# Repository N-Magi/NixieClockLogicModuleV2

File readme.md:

# NixieClockLogicModule v.2

new Version of NixieClock LogicModule mar fix wire ploblem

## How To Use

it's made from platformIo
open project as PIO project then connect to your microContoroller board and upload

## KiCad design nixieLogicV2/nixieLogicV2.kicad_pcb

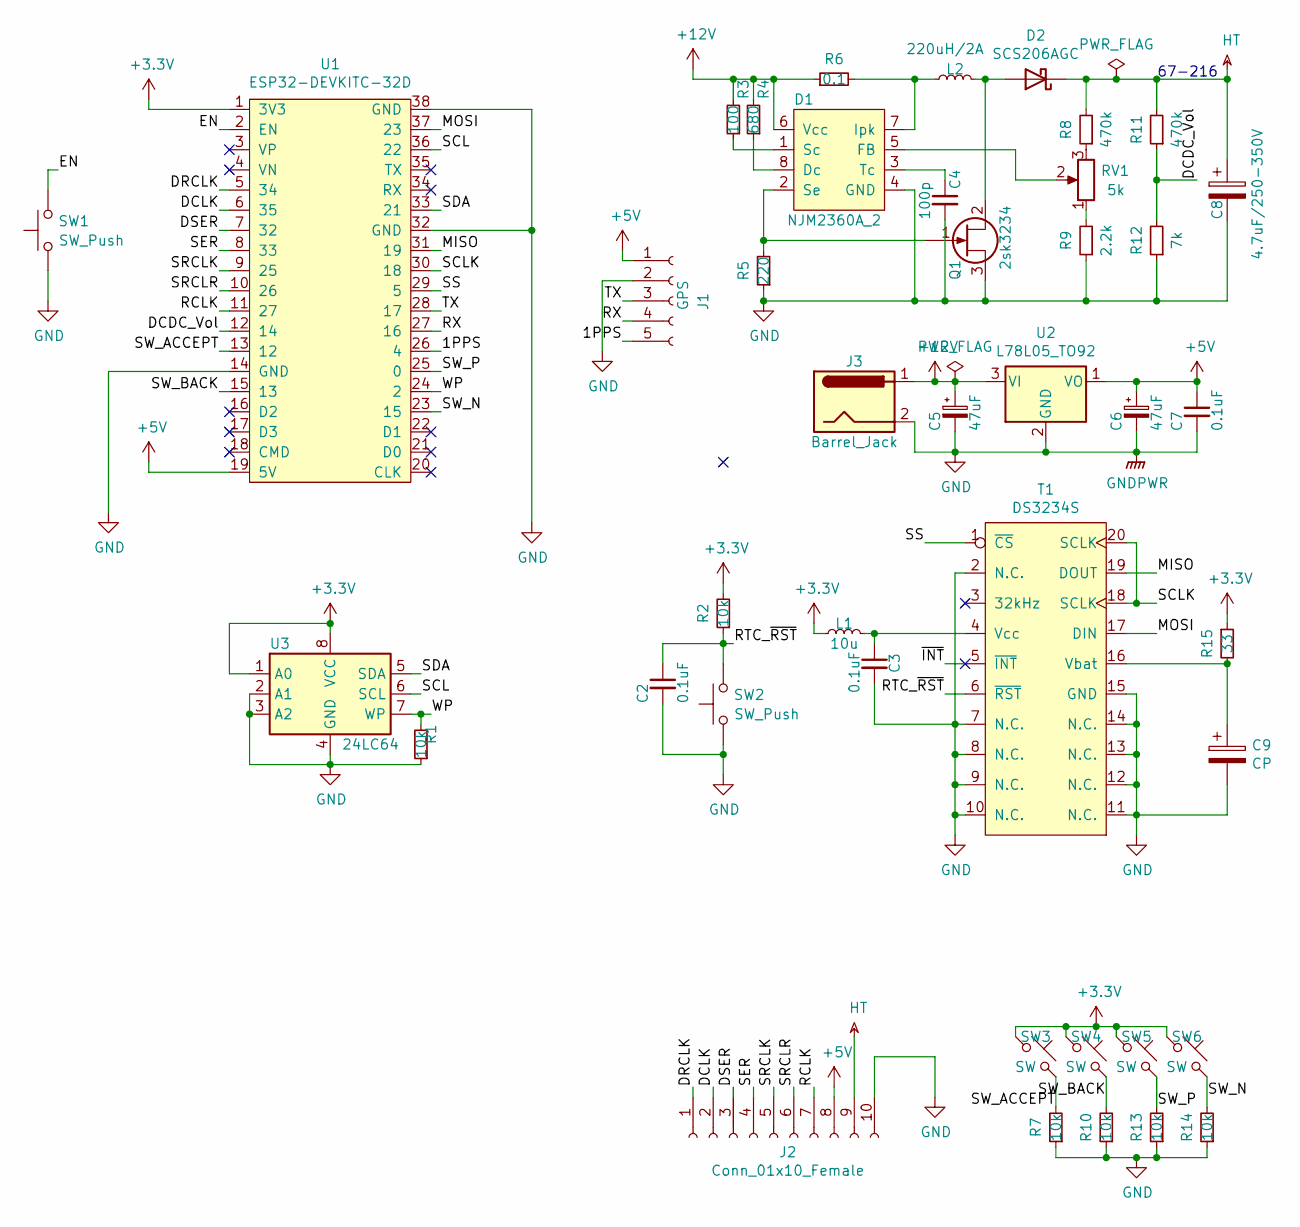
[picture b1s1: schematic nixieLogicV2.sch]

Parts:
C2, C3, C7: 0.1uF; C_0805_2012Metric_Pad1.15x1.40mm_HandSolder
C4: 100p; C_Rect_L7.2mm_W2.5mm_P5.00mm_FKS2_FKP2_MKS2_MKP2
C5, C6: 47uF; CP_Radial_D5.0mm_P2.00mm
C8: 4.7uF/250-350V; CP_Radial_D10.0mm_P5.00mm
C9: CP; CP_Radial_D14.0mm_P5.00mm
D1: NJM2360A_2; DIP-8_W7.62mm_Socket_LongPads
D2: SCS206AGC; TO-220-2_Horizontal_TabDown
J1: GPS; PinHeader_1x05_P2.54mm_Vertical
J2: Conn_01x10_Female; PinHeader_1x10_P2.54mm_Vertical
J3: Barrel_Jack; BarrelJack_Horizontal
L1: 10u; L_1206_3216Metric_Pad1.42x1.75mm_HandSolder
L2: 220uH/2A; L_Toroid_Vertical_L16.0mm_W8.0mm_P7.62mm
Q1: 2sk3234; TO-220-3_Horizontal_TabDown
R1, R2, R7, R10, R13, R14: 10k; R_0805_2012Metric_Pad1.15x1.40mm_HandSolder
R3: 100; R_Axial_DIN0207_L6.3mm_D2.5mm_P7.62mm_Horizontal
R4: 680; R_Axial_DIN0207_L6.3mm_D2.5mm_P7.62mm_Horizontal
R5: 220; R_Axial_DIN0207_L6.3mm_D2.5mm_P7.62mm_Horizontal
R6: 0.1; R_Axial_DIN0207_L6.3mm_D2.5mm_P15.24mm_Horizontal
R8, R11: 470k; R_Axial_DIN0207_L6.3mm_D2.5mm_P7.62mm_Horizontal
R9: 2.2k; R_Axial_DIN0207_L6.3mm_D2.5mm_P7.62mm_Horizontal
R12: 7k; R_Axial_DIN0207_L6.3mm_D2.5mm_P7.62mm_Horizontal
R15: 33; R_Axial_DIN0207_L6.3mm_D2.5mm_P7.62mm_Horizontal
RV1: 5k; Potentiometer_Vishay_T73YP_Vertical
SW1, SW2: SW_Push; SW_PUSH_6mm
SW3, SW4, SW5, SW6: SW; SW_PUSH_6mm
T1: DS3234S; SOIC-20W_7.5x12.8mm_P1.27mm
U1: ESP32-DEVKITC-32D; espWroom32devKit-C
U2: L78L05_TO92; TO-220-3_Horizontal_TabDown
U3: 24LC64; DIP-8_W7.62mm_Socket_LongPads

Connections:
+3V3: L1.1, R2.2, R15.1, SW3.1, SW4.1, SW5.1, SW6.1, U1.1 (3V3), U3.1 (A0), U3.8 (VCC)
+5V: C6.1, C7.1, J1.1, J2.8, U1.19 (5V), U2.1 (VO)
+12V: C5.1, D1.6 (Vcc), J3.1, R3.2, R4.2, R6.1, U2.3 (VI)
/1PPS: J1.5, U1.26 (4)
/DCDC_Vol: R11.1, R12.2, U1.12 (14)
/DCLK: J2.2, U1.6 (35)
/DRCLK: J2.1, U1.5 (34)
/DSER: J2.3, U1.7 (32)
/EN: SW1.2, U1.2 (EN)
/MISO: T1.19 (DOUT), U1.31 (19)
/MOSI: T1.17 (DIN), U1.37 (23)
/RCLK: J2.7, U1.11 (27)
/RTC_~RST: C2.1, R2.1, SW2.2, T1.6 (~RST)
/RX: J1.4, U1.27 (16)
/SCL: U1.36 (22), U3.6 (SCL)
/SCLK: T1.18 (SCLK), T1.20 (SCLK), U1.30 (18)
/SDA: U1.33 (21), U3.5 (SDA)
/SER: J2.4, U1.8 (33)
/SRCLK: J2.5, U1.9 (25)
/SRCLR: J2.6, U1.10 (26)
/SS: T1.1 (~CS), U1.29 (5)
/SW_ACCEPT: R7.2, SW3.2, U1.13 (12)
/SW_BACK: R10.2, SW4.2, U1.15 (13)
/SW_N: R14.2, SW6.2, U1.23 (15)
/SW_P: R13.2, SW5.2, U1.25 (0)
/TX: J1.3, U1.28 (17)
/WP: R1.2, U1.24 (2), U3.7 (WP)
/~INT: T1.5 (~INT)
GND: C2.2, C3.2, C4.2, C5.2, C6.2, C7.2, C8.2, C9.2, D1.4 (GND), J1.2, J2.10, J3.2, J3.3, Q1.3 (S), R1.1, R5.1, R7.1, R9.1, R10.1, R12.1, R13.1, R14.1, SW1.1, SW2.1, T1.2 (N.C.), T1.7 (N.C.), T1.8 (N.C.), T1.9 (N.C.), T1.10 (N.C.), T1.11 (N.C.), T1.12 (N.C.), T1.13 (N.C.), T1.14 (N.C.), T1.15 (GND), U1.14 (GND), U1.32 (GND), U1.38 (GND), U2.2 (GND), U3.2 (A1), U3.3 (A2), U3.4 (GND)
HT: C8.1, D2.1 (K), J2.9, R8.2, R11.2
unnamed: C3.1, L1.2, T1.4 (Vcc)
unnamed: C4.1, D1.3 (Tc)
unnamed: C9.1, R15.2, T1.16 (Vbat)
unnamed: D1.1 (Sc), R3.1
unnamed: D1.2 (Se), Q1.1 (G), R5.2
unnamed: D1.5 (FB), RV1.2
unnamed: D1.7 (Ipk), L2.1, R6.2
unnamed: D1.8 (Dc), R4.1
unnamed: D2.2 (A), L2.2, Q1.2 (D)
unnamed: R8.1, RV1.3
unnamed: R9.2, RV1.1

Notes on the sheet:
67-216

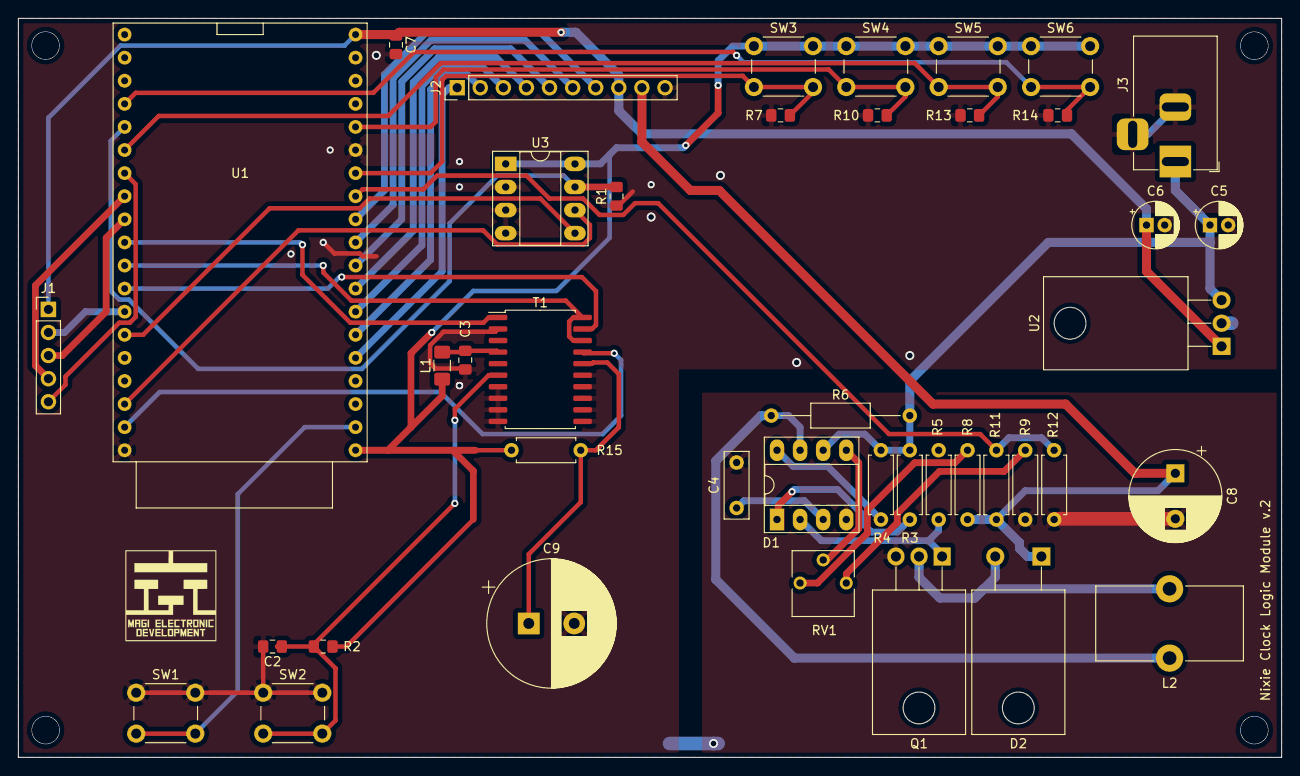
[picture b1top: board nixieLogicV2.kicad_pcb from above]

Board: 2 copper layers, 138.9 x 81.3 mm, 42 parts (0 on the bottom side), 40 nets.

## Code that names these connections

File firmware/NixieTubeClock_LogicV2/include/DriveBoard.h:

#include <Arduino.h>
#include <Wire.h>

#define SW_ACCEPT 12
#define SW_BACK 35
#define SW_N 15
#define SW_P 34
#define Vvol 36

#define EEPROM_SDA 21
#define EEPROM_SCL 22

class DriveBoard
{
private:
    uint8_t p_keyState = 0;

public:
    uint8_t ReadKeyState();
    float MesureVoltage();

    void SetSettingToROM(uint16_t addr, uint8_t* value);
    uint8_t* LoadSettingByROM(uint16_t addr, uint16_t size);

    DriveBoard(/* args */);
    ~DriveBoard();
};

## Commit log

2020-12-06 add FirmWare Currently Ntp Function working need to add config menu
2021-01-09 Add Serial Console System To setting or show status
2021-01-09 Add Function of Serial Console
2022-06-24 add Divergence Clock mode
2022-06-26 Divergence mode added
